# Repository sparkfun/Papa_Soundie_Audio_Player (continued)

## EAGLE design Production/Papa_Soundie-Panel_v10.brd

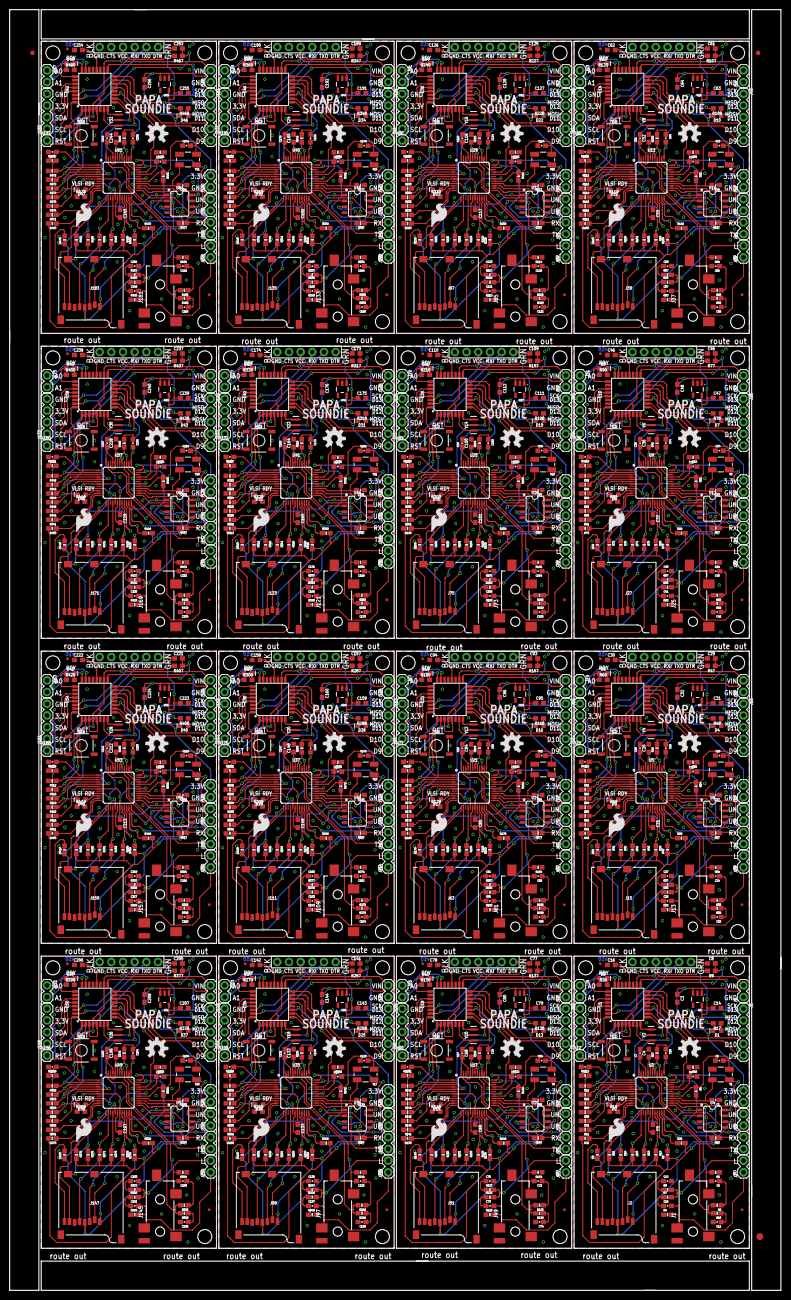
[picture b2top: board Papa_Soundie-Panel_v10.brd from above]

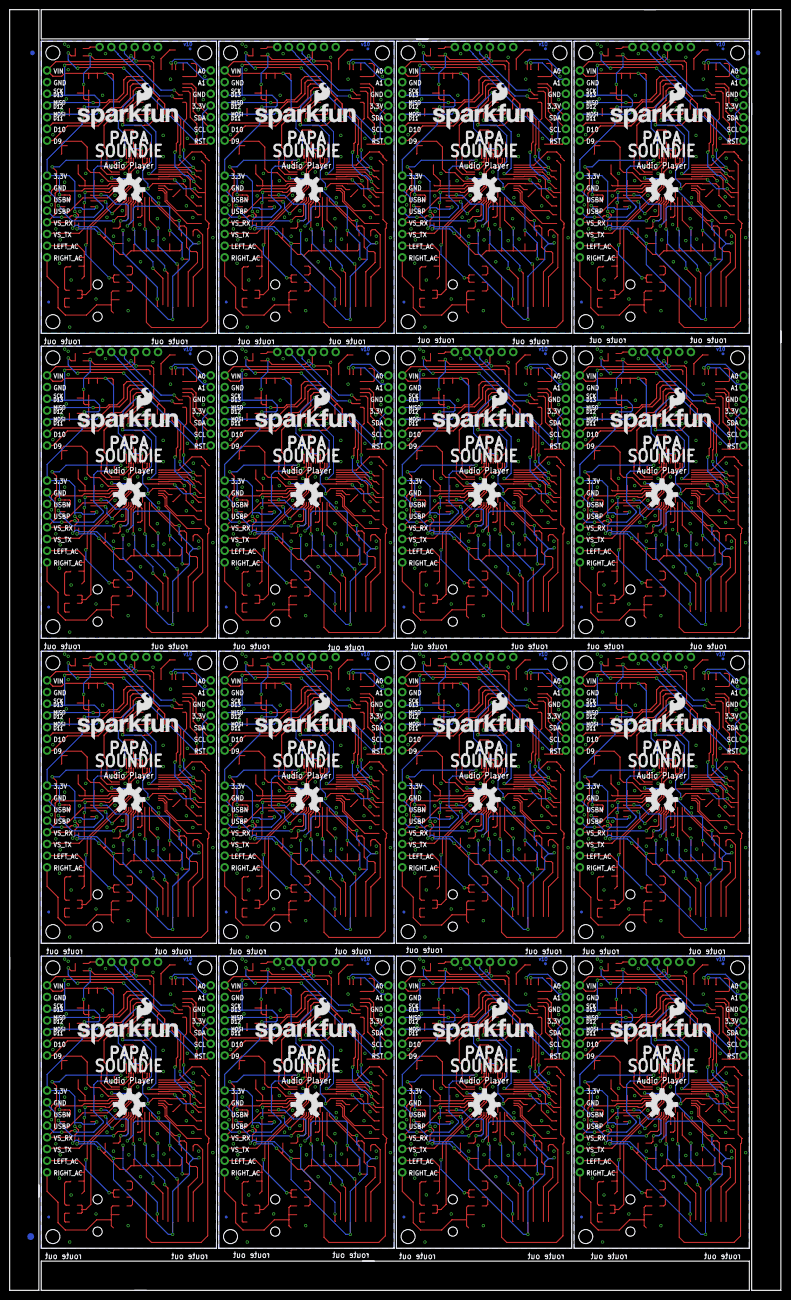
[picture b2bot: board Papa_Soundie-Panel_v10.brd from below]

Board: 2 copper layers, 167.6 x 278.4 mm, 1270 parts (67 on the bottom side), 1024 nets.

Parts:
C1, C2, C17, C18, C33, C34, C49, C50, C65, C66, C81, C82, C97, C98, C113, C114, C129, C130, C145, C146, C161, C162, C177, C178, C193, C194, C209, C210, C225, C226, C241, C242: 22pF; 0603-CAP
C3, C4, C5, C20, C21, C32, C36, C37, C48, C52, C53, C64, C68, C69, C80, C84, C85, C96, C100, C101, C112, C116, C117, C128, C132, C133, C144, C148, C149, C160, C164, C165, C176, C180, C181, C192, C196, C197, C208, C212, C213, C224, C228, C229, C240, C244, C245, C256: 10uF; 0603
C6, C7, C19, C22, C35, C38, C51, C54, C67, C70, C83, C86, C99, C102, C115, C118, C131, C134, C147, C150, C163, C166, C179, C182, C195, C198, C211, C214, C227, C230, C243, C246: 1.0uF; 0603-CAP
C8, C16, C29, C30, C45, C46, C61, C62, C77, C78, C93, C94, C109, C110, C125, C126, C141, C142, C157, C158, C173, C174, C189, C190, C205, C206, C221, C222, C237, C238, C253, C254: 0.1uF; 0603
C9, C10, C13, C23, C24, C25, C39, C40, C41, C55, C56, C57, C71, C72, C73, C87, C88, C89, C103, C104, C105, C119, C120, C121, C135, C136, C137, C151, C152, C153, C167, C168, C169, C183, C184, C185, C199, C200, C201, C215, C216, C217, C231, C232, C233, C247, C248, C249: 10uF; 0603-CAP
C11, C12, C26, C27, C42, C43, C58, C59, C74, C75, C90, C91, C106, C107, C122, C123, C138, C139, C154, C155, C170, C171, C186, C187, C202, C203, C218, C219, C234, C235, C250, C251: 10nF; 0603-CAP
C14, C31, C47, C63, C79, C95, C111, C127, C143, C159, C175, C191, C207, C223, C239, C255: 2.2uF; 0603
C15, C28, C44, C60, C76, C92, C108, C124, C140, C156, C172, C188, C204, C220, C236, C252: 47nF; 0603-CAP
D1, D4, D7, D10, D13, D16, D19, D22, D25, D28, D31, D34, D37, D40, D43, D46: GREEN; LED-0603
D2, D3, D5, D6, D8, D9, D11, D12, D14, D15, D17, D18, D20, D21, D23, D24, D26, D27, D29, D30, D32, D33, D35, D36, D38, D39, D41, D42, D44, D45, D47, D48: RED; LED-0603
E$1, E$2: FIDUCIAL-1.5X3
E$3, E$4, E$6, E$7: FIDUCIAL-1X2
FD1, FD2, FD3, FD4, FD5, FD6, FD7, FD8, FD9, FD10, FD11, FD12, FD13, FD14, FD15, FD16, FD17, FD18, FD19, FD20, FD21, FD22, FD23, FD24, FD25, FD26, FD27, FD28, FD29, FD30, FD31, FD32, FD33, FD34, FD35, FD36, FD37, FD38, FD39, FD40, FD41, FD42, FD43, FD44, FD45, FD46, FD47, FD48, FD49, FD50, FD51, FD52, FD53, FD54, FD55, FD56, FD57, FD58, FD59, FD60, FD61, FD62, FD63, FD64: FIDUCIALUFIDUCIAL; FIDUCIAL-MICRO
H1, H2, H3, H4, H5, H6, H7, H8, H9, H10, H11, H12, H13, H14, H15, H16, H17, H18, H19, H20, H21, H22, H23, H24, H25, H26, H27, H28, H29, H30, H31, H32, H33, H34, H35, H36, H37, H38, H39, H40, H41, H42, H43, H44, H45, H46, H47, H48: STAND-OFFTIGHT; STAND-OFF-TIGHT
J1, J13, J25, J37, J49, J61, J73, J85, J97, J109, J121, J133, J145, J157, J169, J181: Audio Jack; AUDIO-JACK-3.5MM-SMD
J2, J15, J27, J39, J51, J63, J75, J87, J99, J111, J123, J135, J147, J159, J171, J183: MICRO-SD_CARD_SOCKET; MICRO-SD-SOCKET
J3, J5, J8, J9, J10, J11, J18, J19, J20, J21, J22, J23, J30, J31, J32, J33, J34, J35, J42, J43, J44, J45, J46, J47, J54, J55, J56, J57, J58, J59, J66, J67, J68, J69, J70, J71, J78, J79, J80, J81, J82, J83, J90, J91, J92, J93, J94, J95, J102, J103, J104, J105, J106, J107, J114, J115, J116, J117, J118, J119, J126, J127, J128, J129, J130, J131, J138, J139, J140, J141, J142, J143, J150, J151, J152, J153, J154, J155, J162, J163, J164, J165, J166, J167, J174, J175, J176, J177, J178, J179, J186, J187, J188, J189, J190, J191: 1X02
J4, J14, J26, J38, J50, J62, J74, J86, J98, J110, J122, J134, J146, J158, J170, J182: 6_PIN_SERIAL_TARGET_SIDE_W_SILK
J6, J16, J28, J40, J52, J64, J76, J88, J100, J112, J124, J136, J148, J160, J172, J184: 1X05
J7, J17, J29, J41, J53, J65, J77, J89, J101, J113, J125, J137, J149, J161, J173, J185: 1X04
J12, J24, J36, J48, J60, J72, J84, J96, J108, J120, J132, J144, J156, J168, J180, J192: 1X01
LOGO1, LOGO4, LOGO9, LOGO13, LOGO17, LOGO21, LOGO25, LOGO29, LOGO33, LOGO37, LOGO41, LOGO45, LOGO49, LOGO53, LOGO57, LOGO61: OSHW-LOGOL; OSHW-LOGO-L
LOGO2, LOGO5, LOGO10, LOGO14, LOGO18, LOGO22, LOGO26, LOGO30, LOGO34, LOGO38, LOGO42, LOGO46, LOGO50, LOGO54, LOGO58, LOGO62: SFE_LOGO_FLAME.2_INCH; SFE_LOGO_FLAME_.2
LOGO3, LOGO8, LOGO12, LOGO16, LOGO20, LOGO24, LOGO28, LOGO32, LOGO36, LOGO40, LOGO44, LOGO48, LOGO52, LOGO56, LOGO60, LOGO64: OSHW-LOGOL; OSHW-LOGO-M
LOGO6, LOGO7, LOGO11, LOGO15, LOGO19, LOGO23, LOGO27, LOGO31, LOGO35, LOGO39, LOGO43, LOGO47, LOGO51, LOGO55, LOGO59, LOGO63: SFE_LOGO_NAME_FLAME.1_INCH; SFE_LOGO_NAME_FLAME_.2
R1, R14, R15, R32, R61, R62, R91, R92, R121, R122, R151, R152, R181, R182, R211, R212, R241, R242, R271, R272, R301, R302, R331, R332, R361, R362, R391, R392, R421, R422, R451, R452: 1M; 0603-RES
R2, R3, R11, R12, R13, R16, R19, R20, R21, R22, R23, R24, R25, R28, R29, R30, R31, R39, R40, R41, R42, R43, R44, R45, R49, R50, R51, R52, R53, R54, R55, R56, R57, R58, R69, R70, R71, R72, R73, R74, R75, R79, R80, R81, R82, R83, R84, R85, R86, R87, R88, R99, R100, R101, R102, R103, R104, R105, R109, R110, R111, R112, R113, R114, R115, R116, R117, R118, R129, R130, R131, R132, R133, R134, R135, R139, R140, R141, R142, R143, R144, R145, R146, R147, R148, R159, R160, R161, R162, R163, R164, R165, R169, R170, R171, R172, R173, R174, R175, R176, R177, R178, R189, R190, R191, R192, R193, R194, R195, R199, R200, R201, R202, R203, R204, R205, R206, R207, R208, R219, R220, R221, R222, R223, R224, R225, R229, R230, R231, R232, R233, R234, R235, R236, R237, R238, R249, R250, R251, R252, R253, R254, R255, R259, R260, R261, R262, R263, R264, R265, R266, R267, R268, R279, R280, R281, R282, R283, R284, R285, R289, R290, R291, R292, R293, R294, R295, R296, R297, R298, R309, R310, R311, R312, R313, R314, R315, R319, R320, R321, R322, R323, R324, R325, R326, R327, R328, R339, R340, R341, R342, R343, R344, R345, R349, R350, R351, R352, R353, R354, R355, R356, R357, R358, R369, R370, R371, R372, R373, R374, R375, R379, R380, R381, R382, R383, R384, R385, R386, R387, R388, R399, R400, R401, R402, R403, R404, R405, R409, R410, R411, R412, R413, R414, R415, R416, R417, R418, R429, R430, R431, R432, R433, R434, R435, R439, R440, R441, R442, R443, R444, R445, R446, R447, R448, R459, R460, R461, R462, R463, R464, R465, R469, R470, R471, R472, R473, R474, R475, R476, R477, R478: 100k; 0603-RES
R4, R5, R33, R34, R63, R64, R93, R94, R123, R124, R153, R154, R183, R184, R213, R214, R243, R244, R273, R274, R303, R304, R333, R334, R363, R364, R393, R394, R423, R424, R453, R454: 10K; 0603-RES
R6, R7, R35, R36, R65, R66, R95, R96, R125, R126, R155, R156, R185, R186, R215, R216, R245, R246, R275, R276, R305, R306, R335, R336, R365, R366, R395, R396, R425, R426, R455, R456: 470; 0603-RES
R8, R10, R37, R38, R67, R68, R97, R98, R127, R128, R157, R158, R187, R188, R217, R218, R247, R248, R277, R278, R307, R308, R337, R338, R367, R368, R397, R398, R427, R428, R457, R458: 20; 0603-RES
R9, R47, R77, R107, R137, R167, R197, R227, R257, R287, R317, R347, R377, R407, R437, R467: 10k; 0603
R17, R48, R78, R108, R138, R168, R198, R228, R258, R288, R318, R348, R378, R408, R438, R468: 330; 0603
R18, R26, R59, R60, R89, R90, R119, R120, R149, R150, R179, R180, R209, R210, R239, R240, R269, R270, R299, R300, R329, R330, R359, R360, R389, R390, R419, R420, R449, R450, R479, R480: 2.0k; 0603
R27, R46, R76, R106, R136, R166, R196, R226, R256, R286, R316, R346, R376, R406, R436, R466: 10; 0603-RES
S1, S2, S3, S4, S5, S6, S7, S8, S9, S10, S11, S12, S13, S14, S15, S16: RESET; TACTILE_SWITCH_SMD_5.2MM
U1, U6, U10, U14, U18, U22, U26, U30, U34, U38, U42, U46, U50, U54, U58, U62: ATMEGA328P_TQFP; TQFP32-08
U2, U5, U9, U13, U17, U21, U25, U29, U33, U37, U41, U45, U49, U53, U57, U61: VS1000D; LQFP-48
U3, U7, U11, U15, U19, U23, U27, U31, U35, U39, U43, U47, U51, U55, U59, U63: 3.3V; SOT23-5
U4, U8, U12, U16, U20, U24, U28, U32, U36, U40, U44, U48, U52, U56, U60, U64: 4MB Flash; SO08
Y1, Y3, Y5, Y7, Y9, Y11, Y13, Y15, Y17, Y19, Y21, Y23, Y25, Y27, Y29, Y31: 12MHz; CRYSTAL-SMD-5X3
Y2, Y4, Y6, Y8, Y10, Y12, Y14, Y16, Y18, Y20, Y22, Y24, Y26, Y28, Y30, Y32: 8MHz; RESONATOR-SMD-3.2X1.3

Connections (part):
A0: J8.1, U1.23
A1: J8.2, U1.24
A2: J19.1, U6.23
A3: J19.2, U6.24
A4: J31.1, U10.23
A5: J31.2, U10.24
A6: J43.1, U14.23
A7: J43.2, U14.24
A8: J55.1, U18.23
A9: J55.2, U18.24
A10: J67.1, U22.23
A11: J67.2, U22.24
A12: J79.1, U26.23
A13: J79.2, U26.24
A14: J91.1, U30.23
A15: J91.2, U30.24
A16: J103.1, U34.23
A17: J103.2, U34.24
A18: J115.1, U38.23
A19: J115.2, U38.24
A20: J127.1, U42.23
A21: J127.2, U42.24
A22: J139.1, U46.23
A23: J139.2, U46.24
A24: J151.1, U50.23
A25: J151.2, U50.24
A26: J163.1, U54.23
A27: J163.2, U54.24
A28: J175.1, U58.23
A29: J175.2, U58.24
A30: J187.1, U62.23
A31: J187.2, U62.24
AVDD: C4.1, U2.34, U2.39, U2.44, U2.46
AVDD1: C20.1, U5.34, U5.39, U5.44, U5.46
AVDD2: C36.1, U9.34, U9.39, U9.44, U9.46
AVDD3: C52.1, U13.34, U13.39, U13.44, U13.46
AVDD4: C68.1, U17.34, U17.39, U17.44, U17.46
AVDD5: C84.1, U21.34, U21.39, U21.44, U21.46
AVDD6: C100.1, U25.34, U25.39, U25.44, U25.46
AVDD7: C116.1, U29.34, U29.39, U29.44, U29.46
AVDD8: C132.1, U33.34, U33.39, U33.44, U33.46
AVDD9: C148.1, U37.34, U37.39, U37.44, U37.46
AVDD10: C164.1, U41.34, U41.39, U41.44, U41.46
AVDD11: C180.1, U45.34, U45.39, U45.44, U45.46
AVDD12: C196.1, U49.34, U49.39, U49.44, U49.46
AVDD13: C212.1, U53.34, U53.39, U53.44, U53.46
AVDD14: C228.1, U57.34, U57.39, U57.44, U57.46
AVDD15: C244.1, U61.34, U61.39, U61.44, U61.46
CVDD: C6.1, R15.2, U2.32
CVDD1: C22.1, R32.2, U5.32
CVDD2: C38.1, R62.2, U9.32
CVDD3: C54.1, R92.2, U13.32
CVDD4: C70.1, R122.2, U17.32
CVDD5: C86.1, R152.2, U21.32
CVDD6: C102.1, R182.2, U25.32
CVDD7: C118.1, R212.2, U29.32
CVDD8: C134.1, R242.2, U33.32
CVDD9: C150.1, R272.2, U37.32
CVDD10: C166.1, R302.2, U41.32
CVDD11: C182.1, R332.2, U45.32
CVDD12: C198.1, R362.2, U49.32
CVDD13: C214.1, R392.2, U53.32
CVDD14: C230.1, R422.2, U57.32
CVDD15: C246.1, R452.2, U61.32
D1: J16.5, U6.13
D2: J16.4, U6.14
D3: J28.5, U10.13
D4: J28.4, U10.14
D5: J40.5, U14.13
D6: J40.4, U14.14
D7: J52.5, U18.13
D8: J52.4, U18.14
D9: J6.5, U1.13
D10: J6.4, U1.14
D11: J64.5, U22.13
D12: J64.4, U22.14
D13: J76.5, U26.13
D14: J76.4, U26.14
D15: J88.5, U30.13
D16: J88.4, U30.14
D17: J100.5, U34.13
D18: J100.4, U34.14
D19: J112.5, U38.13
D20: J112.4, U38.14
D21: J124.5, U42.13
D22: J124.4, U42.14
D23: J136.5, U46.13
D24: J136.4, U46.14
D25: J148.5, U50.13
D26: J148.4, U50.14
D27: J160.5, U54.13
D28: J160.4, U54.14
D29: J172.5, U58.13
D30: J172.4, U58.14
D31: J184.5, U62.13
D32: J184.4, U62.14
DTR: C8.1, J4.P$1
DTR1: C29.1, J14.P$1
DTR2: C45.1, J26.P$1
DTR3: C61.1, J38.P$1
DTR4: C77.1, J50.P$1
DTR5: C93.1, J62.P$1
DTR6: C109.1, J74.P$1
DTR7: C125.1, J86.P$1
DTR8: C141.1, J98.P$1
DTR9: C157.1, J110.P$1
DTR10: C173.1, J122.P$1
DTR11: C189.1, J134.P$1
DTR12: C205.1, J146.P$1
DTR13: C221.1, J158.P$1
DTR14: C237.1, J170.P$1
DTR15: C253.1, J182.P$1
DVDD: C5.1, R13.2, R16.2, R19.2, R20.2, R21.2, R22.2, R23.2, R24.2, R25.2, U2.7, U2.19, U2.30
DVDD1: C21.1, R39.2, R40.2, R41.2, R42.2, R43.2, R44.2, R45.2, R57.2, R58.2, U5.7, U5.19, U5.30
DVDD2: C37.1, R69.2, R70.2, R71.2, R72.2, R73.2, R74.2, R75.2, R87.2, R88.2, U9.7, U9.19, U9.30
DVDD3: C53.1, R99.2, R100.2, R101.2, R102.2, R103.2, R104.2, R105.2, R117.2, R118.2, U13.7, U13.19, U13.30
DVDD4: C69.1, R129.2, R130.2, R131.2, R132.2, R133.2, R134.2, R135.2, R147.2, R148.2, U17.7, U17.19, U17.30
DVDD5: C85.1, R159.2, R160.2, R161.2, R162.2, R163.2, R164.2, R165.2, R177.2, R178.2, U21.7, U21.19, U21.30
DVDD6: C101.1, R189.2, R190.2, R191.2, R192.2, R193.2, R194.2, R195.2, R207.2, R208.2, U25.7, U25.19, U25.30
DVDD7: C117.1, R219.2, R220.2, R221.2, R222.2, R223.2, R224.2, R225.2, R237.2, R238.2, U29.7, U29.19, U29.30
DVDD8: C133.1, R249.2, R250.2, R251.2, R252.2, R253.2, R254.2, R255.2, R267.2, R268.2, U33.7, U33.19, U33.30
DVDD9: C149.1, R279.2, R280.2, R281.2, R282.2, R283.2, R284.2, R285.2, R297.2, R298.2, U37.7, U37.19, U37.30
DVDD10: C165.1, R309.2, R310.2, R311.2, R312.2, R313.2, R314.2, R315.2, R327.2, R328.2, U41.7, U41.19, U41.30
DVDD11: C181.1, R339.2, R340.2, R341.2, R342.2, R343.2, R344.2, R345.2, R357.2, R358.2, U45.7, U45.19, U45.30
DVDD12: C197.1, R369.2, R370.2, R371.2, R372.2, R373.2, R374.2, R375.2, R387.2, R388.2, U49.7, U49.19, U49.30
DVDD13: C213.1, R399.2, R400.2, R401.2, R402.2, R403.2, R404.2, R405.2, R417.2, R418.2, U53.7, U53.19, U53.30
DVDD14: C229.1, R429.2, R430.2, R431.2, R432.2, R433.2, R434.2, R435.2, R447.2, R448.2, U57.7, U57.19, U57.30
DVDD15: C245.1, R459.2, R460.2, R461.2, R462.2, R463.2, R464.2, R465.2, R477.2, R478.2, U61.7, U61.19, U61.30
GBUF: R27.1, U2.43
GBUF1: R46.1, U5.43
GBUF2: R76.1, U9.43
GBUF3: R106.1, U13.43
GBUF4: R136.1, U17.43
GBUF5: R166.1, U21.43
GBUF6: R196.1, U25.43
GBUF7: R226.1, U29.43
GBUF8: R256.1, U33.43
GBUF9: R286.1, U37.43
GBUF10: R316.1, U41.43
GBUF11: R346.1, U45.43
GBUF12: R376.1, U49.43
GBUF13: R406.1, U53.43
GBUF14: R436.1, U57.43
GBUF15: R466.1, U61.43
GND: C1.1, C2.1, C3.2, C4.2, C5.2, C6.2, C7.2, C11.2, C12.2, C13.2, C14.2, C15.2, C16.1, D1.C, J1.SLEEVE, J2.GND, J2.GND1, J2.GND3, J4.P$5, J4.P$6, J5.1, J7.4, J9.1, R4.1, R5.1, R11.2, R12.2, R15.1, R18.1, R26.1, R28.2, R29.2, R30.2, R31.2, S1.1, U1.3, U1.5, U1.21, U2.6, U2.8, U2.18, U2.31, U2.38, U2.41, U2.42, U2.48, U3.2, U4.4, Y2.2
GND1: C17.1, C18.1, C19.2, C20.2, C21.2, C22.2, C23.2, C26.2, C27.2, C28.2, C30.1, C31.2, C32.2, D4.C, J13.SLEEVE, J14.P$5, J14.P$6, J15.GND, J15.GND1, J15.GND3, J17.4, J20.1, J22.1, R32.1, R33.1, R34.1, R51.2, R52.2, R53.2, R54.2, R55.2, R56.2, R59.1, R60.1, S2.1, U5.6, U5.8, U5.18, U5.31, U5.38, U5.41, U5.42, U5.48, U6.3, U6.5, U6.21, U7.2, U8.4, Y4.2
GND2: C33.1, C34.1, C35.2, C36.2, C37.2, C38.2, C39.2, C42.2, C43.2, C44.2, C46.1, C47.2, C48.2, D7.C, J25.SLEEVE, J26.P$5, J26.P$6, J27.GND, J27.GND1, J27.GND3, J29.4, J32.1, J34.1, R62.1, R63.1, R64.1, R81.2, R82.2, R83.2, R84.2, R85.2, R86.2, R89.1, R90.1, S3.1, U9.6, U9.8, U9.18, U9.31, U9.38, U9.41, U9.42, U9.48, U10.3, U10.5, U10.21, U11.2, U12.4, Y6.2
GND3: C49.1, C50.1, C51.2, C52.2, C53.2, C54.2, C55.2, C58.2, C59.2, C60.2, C62.1, C63.2, C64.2, D10.C, J37.SLEEVE, J38.P$5, J38.P$6, J39.GND, J39.GND1, J39.GND3, J41.4, J44.1, J46.1, R92.1, R93.1, R94.1, R111.2, R112.2, R113.2, R114.2, R115.2, R116.2, R119.1, R120.1, S4.1, U13.6, U13.8, U13.18, U13.31, U13.38, U13.41, U13.42, U13.48, U14.3, U14.5, U14.21, U15.2, U16.4, Y8.2
GND4: C65.1, C66.1, C67.2, C68.2, C69.2, C70.2, C71.2, C74.2, C75.2, C76.2, C78.1, C79.2, C80.2, D13.C, J49.SLEEVE, J50.P$5, J50.P$6, J51.GND, J51.GND1, J51.GND3, J53.4, J56.1, J58.1, R122.1, R123.1, R124.1, R141.2, R142.2, R143.2, R144.2, R145.2, R146.2, R149.1, R150.1, S5.1, U17.6, U17.8, U17.18, U17.31, U17.38, U17.41, U17.42, U17.48, U18.3, U18.5, U18.21, U19.2, U20.4, Y10.2
GND5: C81.1, C82.1, C83.2, C84.2, C85.2, C86.2, C87.2, C90.2, C91.2, C92.2, C94.1, C95.2, C96.2, D16.C, J61.SLEEVE, J62.P$5, J62.P$6, J63.GND, J63.GND1, J63.GND3, J65.4, J68.1, J70.1, R152.1, R153.1, R154.1, R171.2, R172.2, R173.2, R174.2, R175.2, R176.2, R179.1, R180.1, S6.1, U21.6, U21.8, U21.18, U21.31, U21.38, U21.41, U21.42, U21.48, U22.3, U22.5, U22.21, U23.2, U24.4, Y12.2
GND6: C97.1, C98.1, C99.2, C100.2, C101.2, C102.2, C103.2, C106.2, C107.2, C108.2, C110.1, C111.2, C112.2, D19.C, J73.SLEEVE, J74.P$5, J74.P$6, J75.GND, J75.GND1, J75.GND3, J77.4, J80.1, J82.1, R182.1, R183.1, R184.1, R201.2, R202.2, R203.2, R204.2, R205.2, R206.2, R209.1, R210.1, S7.1, U25.6, U25.8, U25.18, U25.31, U25.38, U25.41, U25.42, U25.48, U26.3, U26.5, U26.21, U27.2, U28.4, Y14.2
GND7: C113.1, C114.1, C115.2, C116.2, C117.2, C118.2, C119.2, C122.2, C123.2, C124.2, C126.1, C127.2, C128.2, D22.C, J85.SLEEVE, J86.P$5, J86.P$6, J87.GND, J87.GND1, J87.GND3, J89.4, J92.1, J94.1, R212.1, R213.1, R214.1, R231.2, R232.2, R233.2, R234.2, R235.2, R236.2, R239.1, R240.1, S8.1, U29.6, U29.8, U29.18, U29.31, U29.38, U29.41, U29.42, U29.48, U30.3, U30.5, U30.21, U31.2, U32.4, Y16.2
GND8: C129.1, C130.1, C131.2, C132.2, C133.2, C134.2, C135.2, C138.2, C139.2, C140.2, C142.1, C143.2, C144.2, D25.C, J97.SLEEVE, J98.P$5, J98.P$6, J99.GND, J99.GND1, J99.GND3, J101.4, J104.1, J106.1, R242.1, R243.1, R244.1, R261.2, R262.2, R263.2, R264.2, R265.2, R266.2, R269.1, R270.1, S9.1, U33.6, U33.8, U33.18, U33.31, U33.38, U33.41, U33.42, U33.48, U34.3, U34.5, U34.21, U35.2, U36.4, Y18.2
GND9: C145.1, C146.1, C147.2, C148.2, C149.2, C150.2, C151.2, C154.2, C155.2, C156.2, C158.1, C159.2, C160.2, D28.C, J109.SLEEVE, J110.P$5, J110.P$6, J111.GND, J111.GND1, J111.GND3, J113.4, J116.1, J118.1, R272.1, R273.1, R274.1, R291.2, R292.2, R293.2, R294.2, R295.2, R296.2, R299.1, R300.1, S10.1, U37.6, U37.8, U37.18, U37.31, U37.38, U37.41, U37.42, U37.48, U38.3, U38.5, U38.21, U39.2, U40.4, Y20.2
GND10: C161.1, C162.1, C163.2, C164.2, C165.2, C166.2, C167.2, C170.2, C171.2, C172.2, C174.1, C175.2, C176.2, D31.C, J121.SLEEVE, J122.P$5, J122.P$6, J123.GND, J123.GND1, J123.GND3, J125.4, J128.1, J130.1, R302.1, R303.1, R304.1, R321.2, R322.2, R323.2, R324.2, R325.2, R326.2, R329.1, R330.1, S11.1, U41.6, U41.8, U41.18, U41.31, U41.38, U41.41, U41.42, U41.48, U42.3, U42.5, U42.21, U43.2, U44.4, Y22.2
GND11: C177.1, C178.1, C179.2, C180.2, C181.2, C182.2, C183.2, C186.2, C187.2, C188.2, C190.1, C191.2, C192.2, D34.C, J133.SLEEVE, J134.P$5, J134.P$6, J135.GND, J135.GND1, J135.GND3, J137.4, J140.1, J142.1, R332.1, R333.1, R334.1, R351.2, R352.2, R353.2, R354.2, R355.2, R356.2, R359.1, R360.1, S12.1, U45.6, U45.8, U45.18, U45.31, U45.38, U45.41, U45.42, U45.48, U46.3, U46.5, U46.21, U47.2, U48.4, Y24.2
GND12: C193.1, C194.1, C195.2, C196.2, C197.2, C198.2, C199.2, C202.2, C203.2, C204.2, C206.1, C207.2, C208.2, D37.C, J145.SLEEVE, J146.P$5, J146.P$6, J147.GND, J147.GND1, J147.GND3, J149.4, J152.1, J154.1, R362.1, R363.1, R364.1, R381.2, R382.2, R383.2, R384.2, R385.2, R386.2, R389.1, R390.1, S13.1, U49.6, U49.8, U49.18, U49.31, U49.38, U49.41, U49.42, U49.48, U50.3, U50.5, U50.21, U51.2, U52.4, Y26.2
GND13: C209.1, C210.1, C211.2, C212.2, C213.2, C214.2, C215.2, C218.2, C219.2, C220.2, C222.1, C223.2, C224.2, D40.C, J157.SLEEVE, J158.P$5, J158.P$6, J159.GND, J159.GND1, J159.GND3, J161.4, J164.1, J166.1, R392.1, R393.1, R394.1, R411.2, R412.2, R413.2, R414.2, R415.2, R416.2, R419.1, R420.1, S14.1, U53.6, U53.8, U53.18, U53.31, U53.38, U53.41, U53.42, U53.48, U54.3, U54.5, U54.21, U55.2, U56.4, Y28.2
GND14: C225.1, C226.1, C227.2, C228.2, C229.2, C230.2, C231.2, C234.2, C235.2, C236.2, C238.1, C239.2, C240.2, D43.C, J169.SLEEVE, J170.P$5, J170.P$6, J171.GND, J171.GND1, J171.GND3, J173.4, J176.1, J178.1, R422.1, R423.1, R424.1, R441.2, R442.2, R443.2, R444.2, R445.2, R446.2, R449.1, R450.1, S15.1, U57.6, U57.8, U57.18, U57.31, U57.38, U57.41, U57.42, U57.48, U58.3, U58.5, U58.21, U59.2, U60.4, Y30.2
GND15: C241.1, C242.1, C243.2, C244.2, C245.2, C246.2, C247.2, C250.2, C251.2, C252.2, C254.1, C255.2, C256.2, D46.C, J181.SLEEVE, J182.P$5, J182.P$6, J183.GND, J183.GND1, J183.GND3, J185.4, J188.1, J190.1, R452.1, R453.1, R454.1, R471.2, R472.2, R473.2, R474.2, R475.2, R476.2, R479.1, R480.1, S16.1, U61.6, U61.8, U61.18, U61.31, U61.38, U61.41, U61.42, U61.48, U62.3, U62.5, U62.21, U63.2, U64.4, Y32.2
IO_0: R12.1, U1.32, U2.2
IO_1: R28.1, U1.1, U2.3
IO_2: R29.1, U1.2, U2.4
IO_3: R30.1, U1.9, U2.5
IO_4: R31.1, U1.10, U2.9
IO_5: R52.1, U5.2, U6.32
IO_6: R11.1, U2.11
IO_7: R22.1, U2.12
IO_8: R53.1, U5.3, U6.1
IO_9: R54.1, U5.4, U6.2
IO_10: R55.1, U5.5, U6.9
IO_11: R56.1, U5.9, U6.10
IO_12: R51.1, U5.11
IO_13: R43.1, U5.12
IO_14: R82.1, U9.2, U10.32
IO_15: R83.1, U9.3, U10.1
IO_16: R84.1, U9.4, U10.2
IO_17: R85.1, U9.5, U10.9
IO_18: R86.1, U9.9, U10.10
IO_19: R81.1, U9.11
IO_20: R73.1, U9.12
IO_21: R112.1, U13.2, U14.32
IO_22: R113.1, U13.3, U14.1
IO_23: R114.1, U13.4, U14.2
IO_24: R115.1, U13.5, U14.9
IO_25: R116.1, U13.9, U14.10
IO_26: R111.1, U13.11
IO_27: R103.1, U13.12
IO_28: R142.1, U17.2, U18.32
IO_29: R143.1, U17.3, U18.1
IO_30: R144.1, U17.4, U18.2
IO_31: R145.1, U17.5, U18.9
IO_32: R146.1, U17.9, U18.10
IO_33: R141.1, U17.11
IO_34: R133.1, U17.12
IO_35: R172.1, U21.2, U22.32
IO_36: R173.1, U21.3, U22.1
IO_37: R174.1, U21.4, U22.2
IO_38: R175.1, U21.5, U22.9
IO_39: R176.1, U21.9, U22.10
IO_40: R171.1, U21.11
IO_41: R163.1, U21.12
IO_42: R202.1, U25.2, U26.32
IO_43: R203.1, U25.3, U26.1
IO_44: R204.1, U25.4, U26.2
IO_45: R205.1, U25.5, U26.9
IO_46: R206.1, U25.9, U26.10
IO_47: R201.1, U25.11
IO_48: R193.1, U25.12
IO_49: R232.1, U29.2, U30.32
IO_50: R233.1, U29.3, U30.1
IO_51: R234.1, U29.4, U30.2
IO_52: R235.1, U29.5, U30.9
IO_53: R236.1, U29.9, U30.10
IO_54: R231.1, U29.11
IO_55: R223.1, U29.12
IO_56: R262.1, U33.2, U34.32
IO_57: R263.1, U33.3, U34.1
IO_58: R264.1, U33.4, U34.2
IO_59: R265.1, U33.5, U34.9
IO_60: R266.1, U33.9, U34.10
IO_61: R261.1, U33.11
IO_62: R253.1, U33.12
IO_63: R292.1, U37.2, U38.32
IO_64: R293.1, U37.3, U38.1
IO_65: R294.1, U37.4, U38.2
IO_66: R295.1, U37.5, U38.9
IO_67: R296.1, U37.9, U38.10
IO_68: R291.1, U37.11
IO_69: R283.1, U37.12
IO_70: R322.1, U41.2, U42.32
IO_71: R323.1, U41.3, U42.1
IO_72: R324.1, U41.4, U42.2
IO_73: R325.1, U41.5, U42.9
IO_74: R326.1, U41.9, U42.10
IO_75: R321.1, U41.11
IO_76: R313.1, U41.12
IO_77: R352.1, U45.2, U46.32
IO_78: R353.1, U45.3, U46.1
IO_79: R354.1, U45.4, U46.2
IO_80: R355.1, U45.5, U46.9
IO_81: R356.1, U45.9, U46.10
IO_82: R351.1, U45.11
IO_83: R343.1, U45.12
IO_84: R382.1, U49.2, U50.32
IO_85: R383.1, U49.3, U50.1
IO_86: R384.1, U49.4, U50.2
IO_87: R385.1, U49.5, U50.9
IO_88: R386.1, U49.9, U50.10
IO_89: R381.1, U49.11
IO_90: R373.1, U49.12
IO_91: R412.1, U53.2, U54.32
IO_92: R413.1, U53.3, U54.1
IO_93: R414.1, U53.4, U54.2
IO_94: R415.1, U53.5, U54.9
IO_95: R416.1, U53.9, U54.10
IO_96: R411.1, U53.11
IO_97: R403.1, U53.12
IO_98: R442.1, U57.2, U58.32
IO_99: R443.1, U57.3, U58.1
IO_100: R444.1, U57.4, U58.2
IO_101: R445.1, U57.5, U58.9
IO_102: R446.1, U57.9, U58.10
IO_103: R441.1, U57.11
IO_104: R433.1, U57.12
IO_105: R472.1, U61.2, U62.32
IO_106: R473.1, U61.3, U62.1
IO_107: R474.1, U61.4, U62.2
IO_108: R475.1, U61.5, U62.9
IO_109: R476.1, U61.9, U62.10
IO_110: R471.1, U61.11
IO_111: R463.1, U61.12
LEFT: R6.2, R10.2, U2.47
LEFT1: R35.2, R38.2, U5.47
LEFT2: R65.2, R68.2, U9.47
LEFT3: R95.2, R98.2, U13.47
LEFT4: R125.2, R128.2, U17.47
LEFT5: R155.2, R158.2, U21.47
LEFT6: R185.2, R188.2, U25.47
LEFT7: R215.2, R218.2, U29.47
LEFT8: R245.2, R248.2, U33.47
LEFT9: R275.2, R278.2, U37.47
LEFT10: R305.2, R308.2, U41.47
LEFT11: R335.2, R338.2, U45.47
LEFT12: R365.2, R368.2, U49.47
LEFT13: R395.2, R398.2, U53.47
LEFT14: R425.2, R428.2, U57.47
LEFT15: R455.2, R458.2, U61.47
L_AC: C9.2, J1.TIP, J3.2, R5.2
L_AC1: C24.2, J13.TIP, J18.2, R34.2
L_AC2: C40.2, J25.TIP, J30.2, R64.2
L_AC3: C56.2, J37.TIP, J42.2, R94.2
L_AC4: C72.2, J49.TIP, J54.2, R124.2
L_AC5: C88.2, J61.TIP, J66.2, R154.2
L_AC6: C104.2, J73.TIP, J78.2, R184.2
L_AC7: C120.2, J85.TIP, J90.2, R214.2
L_AC8: C136.2, J97.TIP, J102.2, R244.2
L_AC9: C152.2, J109.TIP, J114.2, R274.2
L_AC10: C168.2, J121.TIP, J126.2, R304.2
L_AC11: C184.2, J133.TIP, J138.2, R334.2
L_AC12: C200.2, J145.TIP, J150.2, R364.2
L_AC13: C216.2, J157.TIP, J162.2, R394.2
L_AC14: C232.2, J169.TIP, J174.2, R424.2
L_AC15: C248.2, J181.TIP, J186.2, R454.2
MISO: J6.2, U1.16
MISO1: J16.2, U6.16
MISO2: J28.2, U10.16
MISO3: J40.2, U14.16
MISO4: J52.2, U18.16
MISO5: J64.2, U22.16
MISO6: J76.2, U26.16
MISO7: J88.2, U30.16
MISO8: J100.2, U34.16
MISO9: J112.2, U38.16
MISO10: J124.2, U42.16
MISO11: J136.2, U46.16
MISO12: J148.2, U50.16
MISO13: J160.2, U54.16
MISO14: J172.2, U58.16
MISO15: J184.2, U62.16
MOSI: J6.3, U1.15
MOSI1: J16.3, U6.15
MOSI2: J28.3, U10.15
MOSI3: J40.3, U14.15
MOSI4: J52.3, U18.15
MOSI5: J64.3, U22.15
MOSI6: J76.3, U26.15
MOSI7: J88.3, U30.15
MOSI8: J100.3, U34.15
MOSI9: J112.3, U38.15
MOSI10: J124.3, U42.15
MOSI11: J136.3, U46.15
MOSI12: J148.3, U50.15
MOSI13: J160.3, U54.15
MOSI14: J172.3, U58.15
MOSI15: J184.3, U62.15
unnamed: C15.1, R27.2
unnamed: C9.1, R6.1
unnamed: C11.1, R10.1
unnamed: C7.1, U2.45
unnamed: U1.7, Y2.1
unnamed: J2.RSV1, R2.2
unnamed: U1.8, Y2.3
unnamed: C10.1, R7.1
unnamed: J2.RSV2, R3.2
unnamed: C12.1, R8.1
unnamed: D3.A, U1.25
unnamed: D2.C, R18.2
unnamed: D2.A, U2.10
unnamed: D3.C, R26.2
unnamed: C19.1, U5.45
unnamed: C16.2, U1.20
unnamed: D1.A, R17.1
unnamed: C24.1, R35.1
unnamed: C26.1, R38.1
unnamed: C25.1, R36.1
unnamed: C27.1, R37.1
unnamed: C28.1, R46.2
unnamed: U6.7, Y4.1
unnamed: U6.8, Y4.3
unnamed: C30.2, U6.20
unnamed: D4.A, R48.1
unnamed: J15.RSV1, R49.2
unnamed: J15.RSV2, R50.2
unnamed: D5.C, R59.2
unnamed: D5.A, U5.10
unnamed: D6.A, U6.25
unnamed: D6.C, R60.2
unnamed: C35.1, U9.45
unnamed: C40.1, R65.1
unnamed: C42.1, R68.1
unnamed: C41.1, R66.1
unnamed: C43.1, R67.1
unnamed: C44.1, R76.2
unnamed: U10.7, Y6.1
unnamed: U10.8, Y6.3
unnamed: C46.2, U10.20
unnamed: D7.A, R78.1
unnamed: J27.RSV1, R79.2
unnamed: J27.RSV2, R80.2
unnamed: D8.C, R89.2
unnamed: D8.A, U9.10
unnamed: D9.A, U10.25
unnamed: D9.C, R90.2
unnamed: C51.1, U13.45
unnamed: C56.1, R95.1
unnamed: C58.1, R98.1
unnamed: C57.1, R96.1
unnamed: C59.1, R97.1
unnamed: C60.1, R106.2
unnamed: U14.7, Y8.1
unnamed: U14.8, Y8.3
unnamed: C62.2, U14.20
unnamed: D10.A, R108.1
unnamed: J39.RSV1, R109.2
unnamed: J39.RSV2, R110.2
unnamed: D11.C, R119.2
unnamed: D11.A, U13.10
unnamed: D12.A, U14.25
unnamed: D12.C, R120.2
unnamed: C67.1, U17.45
unnamed: C72.1, R125.1
unnamed: C74.1, R128.1
unnamed: C73.1, R126.1
unnamed: C75.1, R127.1
unnamed: C76.1, R136.2
unnamed: U18.7, Y10.1
unnamed: U18.8, Y10.3
unnamed: C78.2, U18.20
unnamed: D13.A, R138.1
unnamed: J51.RSV1, R139.2
unnamed: J51.RSV2, R140.2
unnamed: D14.C, R149.2
unnamed: D14.A, U17.10
unnamed: D15.A, U18.25
unnamed: D15.C, R150.2
unnamed: C83.1, U21.45
unnamed: C88.1, R155.1
unnamed: C90.1, R158.1
unnamed: C89.1, R156.1
unnamed: C91.1, R157.1
unnamed: C92.1, R166.2
unnamed: U22.7, Y12.1
unnamed: U22.8, Y12.3
unnamed: C94.2, U22.20
unnamed: D16.A, R168.1
unnamed: J63.RSV1, R169.2
unnamed: J63.RSV2, R170.2
unnamed: D17.C, R179.2
unnamed: D17.A, U21.10
unnamed: D18.A, U22.25
unnamed: D18.C, R180.2
unnamed: C99.1, U25.45
unnamed: C104.1, R185.1
unnamed: C106.1, R188.1
unnamed: C105.1, R186.1
unnamed: C107.1, R187.1
unnamed: C108.1, R196.2
unnamed: U26.7, Y14.1
unnamed: U26.8, Y14.3
unnamed: C110.2, U26.20
unnamed: D19.A, R198.1
unnamed: J75.RSV1, R199.2
unnamed: J75.RSV2, R200.2
unnamed: D20.C, R209.2
unnamed: D20.A, U25.10
unnamed: D21.A, U26.25
unnamed: D21.C, R210.2
unnamed: C115.1, U29.45
unnamed: C120.1, R215.1
unnamed: C122.1, R218.1
unnamed: C121.1, R216.1
unnamed: C123.1, R217.1
unnamed: C124.1, R226.2
unnamed: U30.7, Y16.1
unnamed: U30.8, Y16.3
unnamed: C126.2, U30.20
unnamed: D22.A, R228.1
unnamed: J87.RSV1, R229.2
unnamed: J87.RSV2, R230.2
unnamed: D23.C, R239.2
unnamed: D23.A, U29.10
unnamed: D24.A, U30.25
unnamed: D24.C, R240.2
unnamed: C131.1, U33.45
unnamed: C136.1, R245.1
unnamed: C138.1, R248.1
unnamed: C137.1, R246.1
unnamed: C139.1, R247.1
unnamed: C140.1, R256.2
unnamed: U34.7, Y18.1
unnamed: U34.8, Y18.3
unnamed: C142.2, U34.20
unnamed: D25.A, R258.1
unnamed: J99.RSV1, R259.2
unnamed: J99.RSV2, R260.2
unnamed: D26.C, R269.2
unnamed: D26.A, U33.10
unnamed: D27.A, U34.25
unnamed: D27.C, R270.2
unnamed: C147.1, U37.45
unnamed: C152.1, R275.1
unnamed: C154.1, R278.1
unnamed: C153.1, R276.1
unnamed: C155.1, R277.1
unnamed: C156.1, R286.2
unnamed: U38.7, Y20.1
unnamed: U38.8, Y20.3
unnamed: C158.2, U38.20
unnamed: D28.A, R288.1
unnamed: J111.RSV1, R289.2
unnamed: J111.RSV2, R290.2
unnamed: D29.C, R299.2
unnamed: D29.A, U37.10
unnamed: D30.A, U38.25
unnamed: D30.C, R300.2
unnamed: C163.1, U41.45
unnamed: C168.1, R305.1
unnamed: C170.1, R308.1
unnamed: C169.1, R306.1
unnamed: C171.1, R307.1
unnamed: C172.1, R316.2
unnamed: U42.7, Y22.1
unnamed: U42.8, Y22.3
unnamed: C174.2, U42.20
unnamed: D31.A, R318.1
unnamed: J123.RSV1, R319.2
unnamed: J123.RSV2, R320.2
unnamed: D32.C, R329.2
unnamed: D32.A, U41.10
unnamed: D33.A, U42.25
unnamed: D33.C, R330.2
unnamed: C179.1, U45.45
unnamed: C184.1, R335.1
unnamed: C186.1, R338.1
unnamed: C185.1, R336.1
unnamed: C187.1, R337.1
unnamed: C188.1, R346.2
unnamed: U46.7, Y24.1
unnamed: U46.8, Y24.3
unnamed: C190.2, U46.20
unnamed: D34.A, R348.1
unnamed: J135.RSV1, R349.2
unnamed: J135.RSV2, R350.2
unnamed: D35.C, R359.2
unnamed: D35.A, U45.10
unnamed: D36.A, U46.25
unnamed: D36.C, R360.2
unnamed: C195.1, U49.45
unnamed: C200.1, R365.1
unnamed: C202.1, R368.1
unnamed: C201.1, R366.1
unnamed: C203.1, R367.1
unnamed: C204.1, R376.2
unnamed: U50.7, Y26.1
unnamed: U50.8, Y26.3
unnamed: C206.2, U50.20
unnamed: D37.A, R378.1
unnamed: J147.RSV1, R379.2
unnamed: J147.RSV2, R380.2
unnamed: D38.C, R389.2
unnamed: D38.A, U49.10
unnamed: D39.A, U50.25
unnamed: D39.C, R390.2
unnamed: C211.1, U53.45
unnamed: C216.1, R395.1
unnamed: C218.1, R398.1
unnamed: C217.1, R396.1
unnamed: C219.1, R397.1
unnamed: C220.1, R406.2
unnamed: U54.7, Y28.1
unnamed: U54.8, Y28.3
unnamed: C222.2, U54.20
unnamed: D40.A, R408.1
unnamed: J159.RSV1, R409.2
unnamed: J159.RSV2, R410.2
unnamed: D41.C, R419.2
unnamed: D41.A, U53.10
unnamed: D42.A, U54.25
unnamed: D42.C, R420.2
unnamed: C227.1, U57.45
unnamed: C232.1, R425.1
unnamed: C234.1, R428.1
unnamed: C233.1, R426.1
unnamed: C235.1, R427.1
unnamed: C236.1, R436.2
unnamed: U58.7, Y30.1
unnamed: U58.8, Y30.3
unnamed: C238.2, U58.20
unnamed: D43.A, R438.1
unnamed: J171.RSV1, R439.2
unnamed: J171.RSV2, R440.2
unnamed: D44.C, R449.2
unnamed: D44.A, U57.10
unnamed: D45.A, U58.25
unnamed: D45.C, R450.2
unnamed: C243.1, U61.45
unnamed: C248.1, R455.1
unnamed: C250.1, R458.1
unnamed: C249.1, R456.1
unnamed: C251.1, R457.1
unnamed: C252.1, R466.2
unnamed: U62.7, Y32.1
unnamed: U62.8, Y32.3
unnamed: C254.2, U62.20
unnamed: D46.A, R468.1
unnamed: J183.RSV1, R469.2
unnamed: J183.RSV2, R470.2
unnamed: D47.C, R479.2
unnamed: D47.A, U61.10
unnamed: D48.A, U62.25
unnamed: D48.C, R480.2
PWRBTN: U1.11, U2.37
PWRBTN1: U5.37, U6.11
PWRBTN2: U9.37, U10.11
PWRBTN3: U13.37, U14.11
PWRBTN4: U17.37, U18.11
PWRBTN5: U21.37, U22.11
PWRBTN6: U25.37, U26.11
PWRBTN7: U29.37, U30.11
PWRBTN8: U33.37, U34.11
PWRBTN9: U37.37, U38.11
PWRBTN10: U41.37, U42.11
PWRBTN11: U45.37, U46.11
PWRBTN12: U49.37, U50.11
PWRBTN13: U53.37, U54.11
PWRBTN14: U57.37, U58.11
PWRBTN15: U61.37, U62.11
RAW: C3.1, J4.P$4, J9.2, U2.33, U3.1, U3.3
RAW1: C32.1, J14.P$4, J20.2, U5.33, U7.1, U7.3
RAW2: C48.1, J26.P$4, J32.2, U9.33, U11.1, U11.3
RAW3: C64.1, J38.P$4, J44.2, U13.33, U15.1, U15.3
RAW4: C80.1, J50.P$4, J56.2, U17.33, U19.1, U19.3
RAW5: C96.1, J62.P$4, J68.2, U21.33, U23.1, U23.3
RAW6: C112.1, J74.P$4, J80.2, U25.33, U27.1, U27.3
RAW7: C128.1, J86.P$4, J92.2, U29.33, U31.1, U31.3
RAW8: C144.1, J98.P$4, J104.2, U33.33, U35.1, U35.3
RAW9: C160.1, J110.P$4, J116.2, U37.33, U39.1, U39.3
RAW10: C176.1, J122.P$4, J128.2, U41.33, U43.1, U43.3
RAW11: C192.1, J134.P$4, J140.2, U45.33, U47.1, U47.3
RAW12: C208.1, J146.P$4, J152.2, U49.33, U51.1, U51.3
RAW13: C224.1, J158.P$4, J164.2, U53.33, U55.1, U55.3
RAW14: C240.1, J170.P$4, J176.2, U57.33, U59.1, U59.3
RAW15: C256.1, J182.P$4, J188.2, U61.33, U63.1, U63.3
RIGHT: R7.2, R8.2, U2.40
RIGHT1: R36.2, R37.2, U5.40
RIGHT2: R66.2, R67.2, U9.40
RIGHT3: R96.2, R97.2, U13.40
RIGHT4: R126.2, R127.2, U17.40
RIGHT5: R156.2, R157.2, U21.40
RIGHT6: R186.2, R187.2, U25.40
RIGHT7: R216.2, R217.2, U29.40
RIGHT8: R246.2, R247.2, U33.40
RIGHT9: R276.2, R277.2, U37.40
RIGHT10: R306.2, R307.2, U41.40
RIGHT11: R336.2, R337.2, U45.40
RIGHT12: R366.2, R367.2, U49.40
RIGHT13: R396.2, R397.2, U53.40
RIGHT14: R426.2, R427.2, U57.40
RIGHT15: R456.2, R457.2, U61.40
RST: C8.2, J12.1, R9.1, S1.3, U1.29
RST1: C29.2, J24.1, R47.1, S2.3, U6.29
RST2: C45.2, J36.1, R77.1, S3.3, U10.29
RST3: C61.2, J48.1, R107.1, S4.3, U14.29
RST4: C77.2, J60.1, R137.1, S5.3, U18.29
RST5: C93.2, J72.1, R167.1, S6.3, U22.29
RST6: C109.2, J84.1, R197.1, S7.3, U26.29
RST7: C125.2, J96.1, R227.1, S8.3, U30.29
RST8: C141.2, J108.1, R257.1, S9.3, U34.29
RST9: C157.2, J120.1, R287.1, S10.3, U38.29
RST10: C173.2, J132.1, R317.1, S11.3, U42.29
RST11: C189.2, J144.1, R347.1, S12.3, U46.29
RST12: C205.2, J156.1, R377.1, S13.3, U50.29
RST13: C221.2, J168.1, R407.1, S14.3, U54.29
RST14: C237.2, J180.1, R437.1, S15.3, U58.29
RST15: C253.2, J192.1, R467.1, S16.3, U62.29
RXI: J4.P$3, U1.30
RXI1: J14.P$3, U6.30
RXI2: J26.P$3, U10.30
RXI3: J38.P$3, U14.30
RXI4: J50.P$3, U18.30
RXI5: J62.P$3, U22.30
RXI6: J74.P$3, U26.30
RXI7: J86.P$3, U30.30
RXI8: J98.P$3, U34.30
RXI9: J110.P$3, U38.30
RXI10: J122.P$3, U42.30
RXI11: J134.P$3, U46.30
RXI12: J146.P$3, U50.30
RXI13: J158.P$3, U54.30
RXI14: J170.P$3, U58.30
RXI15: J182.P$3, U62.30
R_AC: C10.2, J1.RING, J3.1, R4.2
R_AC1: C25.2, J13.RING, J18.1, R33.2
R_AC2: C41.2, J25.RING, J30.1, R63.2
R_AC3: C57.2, J37.RING, J42.1, R93.2
R_AC4: C73.2, J49.RING, J54.1, R123.2
R_AC5: C89.2, J61.RING, J66.1, R153.2
R_AC6: C105.2, J73.RING, J78.1, R183.2
R_AC7: C121.2, J85.RING, J90.1, R213.2
R_AC8: C137.2, J97.RING, J102.1, R243.2
R_AC9: C153.2, J109.RING, J114.1, R273.2
R_AC10: C169.2, J121.RING, J126.1, R303.2
R_AC11: C185.2, J133.RING, J138.1, R333.2
R_AC12: C201.2, J145.RING, J150.1, R363.2
R_AC13: C217.2, J157.RING, J162.1, R393.2
R_AC14: C233.2, J169.RING, J174.1, R423.2
R_AC15: C249.2, J181.RING, J186.1, R453.2
SCK: J6.1, R17.2, U1.17
SCK1: J16.1, R48.2, U6.17
SCK2: J28.1, R78.2, U10.17
SCK3: J40.1, R108.2, U14.17
SCK4: J52.1, R138.2, U18.17
SCK5: J64.1, R168.2, U22.17
SCK6: J76.1, R198.2, U26.17
SCK7: J88.1, R228.2, U30.17
SCK8: J100.1, R258.2, U34.17
SCK9: J112.1, R288.2, U38.17
SCK10: J124.1, R318.2, U42.17
SCK11: J136.1, R348.2, U46.17
SCK12: J148.1, R378.2, U50.17
SCK13: J160.1, R408.2, U54.17
SCK14: J172.1, R438.2, U58.17
SCK15: J184.1, R468.2, U62.17
SCL: J7.1, U1.28
SCL1: J17.1, U6.28
SCL2: J29.1, U10.28
SCL3: J41.1, U14.28
SCL4: J53.1, U18.28
SCL5: J65.1, U22.28
SCL6: J77.1, U26.28
SCL7: J89.1, U30.28
SCL8: J101.1, U34.28
SCL9: J113.1, U38.28
SCL10: J125.1, U42.28
SCL11: J137.1, U46.28
SCL12: J149.1, U50.28
SCL13: J161.1, U54.28
SCL14: J173.1, U58.28
SCL15: J185.1, U62.28
SCLK: U2.23, U4.6
SCLK1: U5.23, U8.6
SCLK2: U9.23, U12.6
SCLK3: U13.23, U16.6
SCLK4: U17.23, U20.6
SCLK5: U21.23, U24.6
SCLK6: U25.23, U28.6
SCLK7: U29.23, U32.6
SCLK8: U33.23, U36.6
SCLK9: U37.23, U40.6
SCLK10: U41.23, U44.6
SCLK11: U45.23, U48.6
SCLK12: U49.23, U52.6
SCLK13: U53.23, U56.6
SCLK14: U57.23, U60.6
SCLK15: U61.23, U64.6
SDA: J7.2, U1.27
SDA1: J17.2, U6.27
SDA2: J29.2, U10.27
SDA3: J41.2, U14.27
SDA4: J53.2, U18.27
SDA5: J65.2, U22.27
SDA6: J77.2, U26.27
SDA7: J89.2, U30.27
SDA8: J101.2, U34.27
SDA9: J113.2, U38.27
SDA10: J125.2, U42.27
SDA11: J137.2, U46.27
SDA12: J149.2, U50.27
SDA13: J161.2, U54.27
SDA14: J173.2, U58.27
SDA15: J185.2, U62.27
SDCD: J2.CD1, R24.1, U2.21
SDCD1: J15.CD1, R45.1, U5.21
SDCD2: J27.CD1, R75.1, U9.21
SDCD3: J39.CD1, R105.1, U13.21
SDCD4: J51.CD1, R135.1, U17.21
SDCD5: J63.CD1, R165.1, U21.21
SDCD6: J75.CD1, R195.1, U25.21
SDCD7: J87.CD1, R225.1, U29.21
SDCD8: J99.CD1, R255.1, U33.21
SDCD9: J111.CD1, R285.1, U37.21
SDCD10: J123.CD1, R315.1, U41.21
SDCD11: J135.CD1, R345.1, U45.21
SDCD12: J147.CD1, R375.1, U49.21
SDCD13: J159.CD1, R405.1, U53.21
SDCD14: J171.CD1, R435.1, U57.21
SDCD15: J183.CD1, R465.1, U61.21
SDCK: J2.SCLK, R20.1, U2.14
SDCK1: J15.SCLK, R41.1, U5.14
SDCK2: J27.SCLK, R71.1, U9.14
SDCK3: J39.SCLK, R101.1, U13.14
SDCK4: J51.SCLK, R131.1, U17.14
SDCK5: J63.SCLK, R161.1, U21.14
SDCK6: J75.SCLK, R191.1, U25.14
SDCK7: J87.SCLK, R221.1, U29.14
SDCK8: J99.SCLK, R251.1, U33.14
SDCK9: J111.SCLK, R281.1, U37.14
SDCK10: J123.SCLK, R311.1, U41.14
SDCK11: J135.SCLK, R341.1, U45.14
SDCK12: J147.SCLK, R371.1, U49.14
SDCK13: J159.SCLK, R401.1, U53.14
SDCK14: J171.SCLK, R431.1, U57.14
SDCK15: J183.SCLK, R461.1, U61.14
SDDI: J2.DI, R19.1, U2.16
SDDI1: J15.DI, R40.1, U5.16
SDDI2: J27.DI, R70.1, U9.16
SDDI3: J39.DI, R100.1, U13.16
SDDI4: J51.DI, R130.1, U17.16
SDDI5: J63.DI, R160.1, U21.16
SDDI6: J75.DI, R190.1, U25.16
SDDI7: J87.DI, R220.1, U29.16
SDDI8: J99.DI, R250.1, U33.16
SDDI9: J111.DI, R280.1, U37.16
SDDI10: J123.DI, R310.1, U41.16
SDDI11: J135.DI, R340.1, U45.16
SDDI12: J147.DI, R370.1, U49.16
SDDI13: J159.DI, R400.1, U53.16
SDDI14: J171.DI, R430.1, U57.16
SDDI15: J183.DI, R460.1, U61.16
SDDO: J2.DO, R21.1, U2.13
SDDO1: J15.DO, R42.1, U5.13
SDDO2: J27.DO, R72.1, U9.13
SDDO3: J39.DO, R102.1, U13.13
SDDO4: J51.DO, R132.1, U17.13
SDDO5: J63.DO, R162.1, U21.13
SDDO6: J75.DO, R192.1, U25.13
SDDO7: J87.DO, R222.1, U29.13
SDDO8: J99.DO, R252.1, U33.13
SDDO9: J111.DO, R282.1, U37.13
SDDO10: J123.DO, R312.1, U41.13
SDDO11: J135.DO, R342.1, U45.13
SDDO12: J147.DO, R372.1, U49.13
SDDO13: J159.DO, R402.1, U53.13
SDDO14: J171.DO, R432.1, U57.13
SDDO15: J183.DO, R462.1, U61.13
SDXCS: J2.CS, R13.1, U2.20
SDXCS1: J15.CS, R39.1, U5.20
SDXCS2: J27.CS, R69.1, U9.20
SDXCS3: J39.CS, R99.1, U13.20
SDXCS4: J51.CS, R129.1, U17.20
SDXCS5: J63.CS, R159.1, U21.20
SDXCS6: J75.CS, R189.1, U25.20
SDXCS7: J87.CS, R219.1, U29.20
SDXCS8: J99.CS, R249.1, U33.20
SDXCS9: J111.CS, R279.1, U37.20
SDXCS10: J123.CS, R309.1, U41.20
SDXCS11: J135.CS, R339.1, U45.20
SDXCS12: J147.CS, R369.1, U49.20
SDXCS13: J159.CS, R399.1, U53.20
SDXCS14: J171.CS, R429.1, U57.20
SDXCS15: J183.CS, R459.1, U61.20
SI: U2.24, U4.2
SI1: U5.24, U8.2
SI2: U9.24, U12.2
SI3: U13.24, U16.2
SI4: U17.24, U20.2
SI5: U21.24, U24.2
SI6: U25.24, U28.2
SI7: U29.24, U32.2
SI8: U33.24, U36.2
SI9: U37.24, U40.2
SI10: U41.24, U44.2
SI11: U45.24, U48.2
SI12: U49.24, U52.2
SI13: U53.24, U56.2
SI14: U57.24, U60.2
SI15: U61.24, U64.2
SO: U2.25, U4.5
SO1: U5.25, U8.5
SO2: U9.25, U12.5
SO3: U13.25, U16.5
SO4: U17.25, U20.5
SO5: U21.25, U24.5
SO6: U25.25, U28.5
SO7: U29.25, U32.5
SO8: U33.25, U36.5
SO9: U37.25, U40.5
SO10: U41.25, U44.5
SO11: U45.25, U48.5
SO12: U49.25, U52.5
SO13: U53.25, U56.5
SO14: U57.25, U60.5
SO15: U61.25, U64.5
TXO: J4.P$2, U1.31
TXO1: J14.P$2, U6.31
TXO2: J26.P$2, U10.31
TXO3: J38.P$2, U14.31
TXO4: J50.P$2, U18.31
TXO5: J62.P$2, U22.31
TXO6: J74.P$2, U26.31
TXO7: J86.P$2, U30.31
TXO8: J98.P$2, U34.31
TXO9: J110.P$2, U38.31
TXO10: J122.P$2, U42.31
TXO11: J134.P$2, U46.31
TXO12: J146.P$2, U50.31
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
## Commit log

2017-11-13 trying something new
2017-11-14 final layout
2017-11-14 added pull-up resistor on XCS line
2017-12-05 added measurement to third standoff
2017-12-06 changes per QC Review
2017-12-06 Fixing issues per QC review
2017-12-30 Add VS1000 Module firmware
2017-12-30 Add SDPlayer.coff for production
2017-12-30 Add 2 Button GPIO example
2018-01-01 Remove open files when IDE is opened
2018-01-04 Updated design for rev 2
2018-01-11 Updated Version No., removed ground connection from SD Card, v03
2018-01-28 Add Power control and LED status
    - Control VS1000 with arduino GPIO pin pulse
    - Turn on Arduino status LED
2018-01-28 Add VS1000 status LED
2018-02-12 fixing enable line, SD3V3
2018-02-13 Add Missing static libraries
2018-02-13 Add WAV file extension
2018-02-13 Remove unused projects
2018-02-13 updated version no V10
2018-02-13 updating silk, cleaning sch
2018-02-13 fixed DRC issues
2018-02-26 created panel v10
2018-03-16 converting Arduino Sketch to Library
2018-04-14 Reformat all code
2018-04-15 Updating src
2018-04-18 updating hardware example project for hookup guide
2018-04-18 Fix file names
2018-04-27 Updating ReadMe with part specific data
    Updated template ReadMe with part specific data (links, skus, etc.
2018-07-26 Updated input voltage range
